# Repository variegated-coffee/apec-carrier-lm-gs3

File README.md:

# APEC Carrier Board for the La Marzocco GS3

*APEC carrier board R1A, rendered in KiCad.*

Espresso electronics are usually proprietary affairs with little to no expandability. The purpose of this project is to give everyone an open source alternative with lots of features and flexibility.

This board is a carrier for the [APEC SoM](https://github.com/variegated-coffee/apec-som), the All Purpose Espresso Controller System-on-Module. It replaces the control board of a La Marzocco GS3: it fits the machine's mains, sensor and actuator wiring, and the SoM does the rest. The SoM provides the RP2350B microcontroller, the ESP32-C6 radio, the ADS124S08 ADC, the FDC1004 capacitance-to-digital converter and a USB hub.

This project isn't affiliated with or endorsed by La Marzocco. "La Marzocco" and "GS3" are used only to say which machine the board is designed for.

## High-level features

* Mains side, on a 13-position terminal block (J2):
  * Three mechanical relays for the group, fill and tea solenoids (U9–U11, Panasonic ALDP112)
  * A 16 A relay for the stock rotary pump (K1)
  * On-board fuse (5×20 mm, clips F2/F3) and varistors on every switched output
  * On-board 12 V, 10 W AC/DC module (U5) for the low-voltage side
* Two SSR control outputs for the brew and service boilers (CN10, CN11)
* Isolated 24 V section, fed from an external 24 V supply (J5):
  * Two low-side switched 24 V outputs for (proportional) solenoids (CN13, CN14), driven through an ADuM3221 isolated gate driver - primarily intended for a proportional steam valve
  * A gear pump connector (CN9) with 5 V speed, direction and tacho signals, made for the FG304
* Sensors:
  * Two RTD inputs (PT1000, ratiometric, on the SoM's ADS124S08)
  * Two pressure transducer inputs (0.5–4.5 V, 5 V supply)
  * Two load cell inputs on an NAU7802 24-bit ADC, with their own ground
  * Two capacitive level inputs (tank and boiler) on the SoM's FDC1004
  * Flow meter, paddle switch and potentiometer inputs
* Display and expansion:
  * EyeSPI connectors for a display module (J13 2×10 header and J17 18-pin FFC) - preferably the [APEC LM GS3 HMI Module](https://github.com/variegated-coffee/apec-lm-gs3-hmi-module)
  * Two Qwiic connectors, a 4-pin I2C header, and a DS3231 RTC with a battery connector
  * microSD card slot
  * UART connector, pin compatible with the LM IoT module (J6)
* USB-C for programming and debugging. The board runs from USB alone for bench work.
* SWD header and a Femtoprobe footprint for the RP2350, and buttons for the RP2350's BOOTSEL and reset and the ESP32-C6's reset and boot mode
* Status LEDs for every output and power rail

[ENGINEERING-NOTES.md](ENGINEERING-NOTES.md) has the details, [IO.md](IO.md) the GPIO assignments, [MANUFACTURING-NOTES.md](MANUFACTURING-NOTES.md) how to build one, and [docs/INSTALLATION.md](docs/INSTALLATION.md) how to install it in a GS3.

## Project status

The current revision is R1A. It hasn't been manufactured yet; EV2 is the most recent revision that has been built. [CHANGELOG.md](CHANGELOG.md) lists what changed between revisions.

There are a few changes between EV2 and R1A, so at this time, rather than manufacturing this yourself, you should probably check in with the Variegated Coffee Discord server to see if someone is willing to share the risk.

The firmware is [developed separately](https://github.com/variegated-coffee/variegated-rs).

## ⚠️ Safety warning

This board switches mains voltage. It is intended to be installed inside an espresso machine, which also uses high-pressure hot water and steam. Mistakes in designing, building, wiring, or programming the board or the machine can cause electric shock, fire, burns, or scalding.

Mains voltage is present on the board whenever the machine is plugged in, including on the neutral side, which can carry line voltage with an unpolarised plug. Never work on the board or handle it while it's connected to mains. Never power it from mains outside a closed, earthed enclosure.

This board is not a safety component. Safety-critical protections, such as thermal cutouts, pressure relief and the machine's own fuses, must be kept and must work independently of this board and its firmware. Only build or use it if you are competent with mains electrical work and pressurised systems, and follow local electrical regulations.

## Notice

This repository contains design files only. It is not a finished product, and it has not been tested or certified for compliance with any regulation, including but not limited to CE, UKCA or FCC requirements.

Anyone who manufactures, assembles, or places a product based on these files on the market does so as the manufacturer of that product, and is solely responsible for its safety, conformity assessment, marking, documentation, and any legal obligations that follow. If you build or use it yourself, you do so at your own risk.

The APEC SoM includes a 2.4 GHz radio transceiver (ESP32-C6). Products using it are subject to radio equipment regulations in addition to other applicable requirements.

The designs are provided “as is” under the CERN-OHL-P v2. See sections 5.1 and 5.2 for the disclaimer of warranty and limitation of liability.

## Opening the design

The project is made with KiCad 10. Every library the design needs is either in this repository or a KiCad standard library, so it opens without extra setup. A few parts exist only as copies embedded in the schematic and PCB, because their library files can't be redistributed. KiCad reports their libraries as missing, which is expected. See [THIRD_PARTY.md](THIRD_PARTY.md).

Vendor 3D models aren't included either. [3d-models/README.md](3d-models/README.md) lists where to download them for complete 3D views.

## License

The design files and documentation in this repository are licensed under the CERN Open Hardware Licence Version 2 – Permissive (CERN-OHL-P-2.0); see [LICENSE.txt](LICENSE.txt).

Some library files come from third parties and keep their own licences; see [THIRD_PARTY.md](THIRD_PARTY.md).

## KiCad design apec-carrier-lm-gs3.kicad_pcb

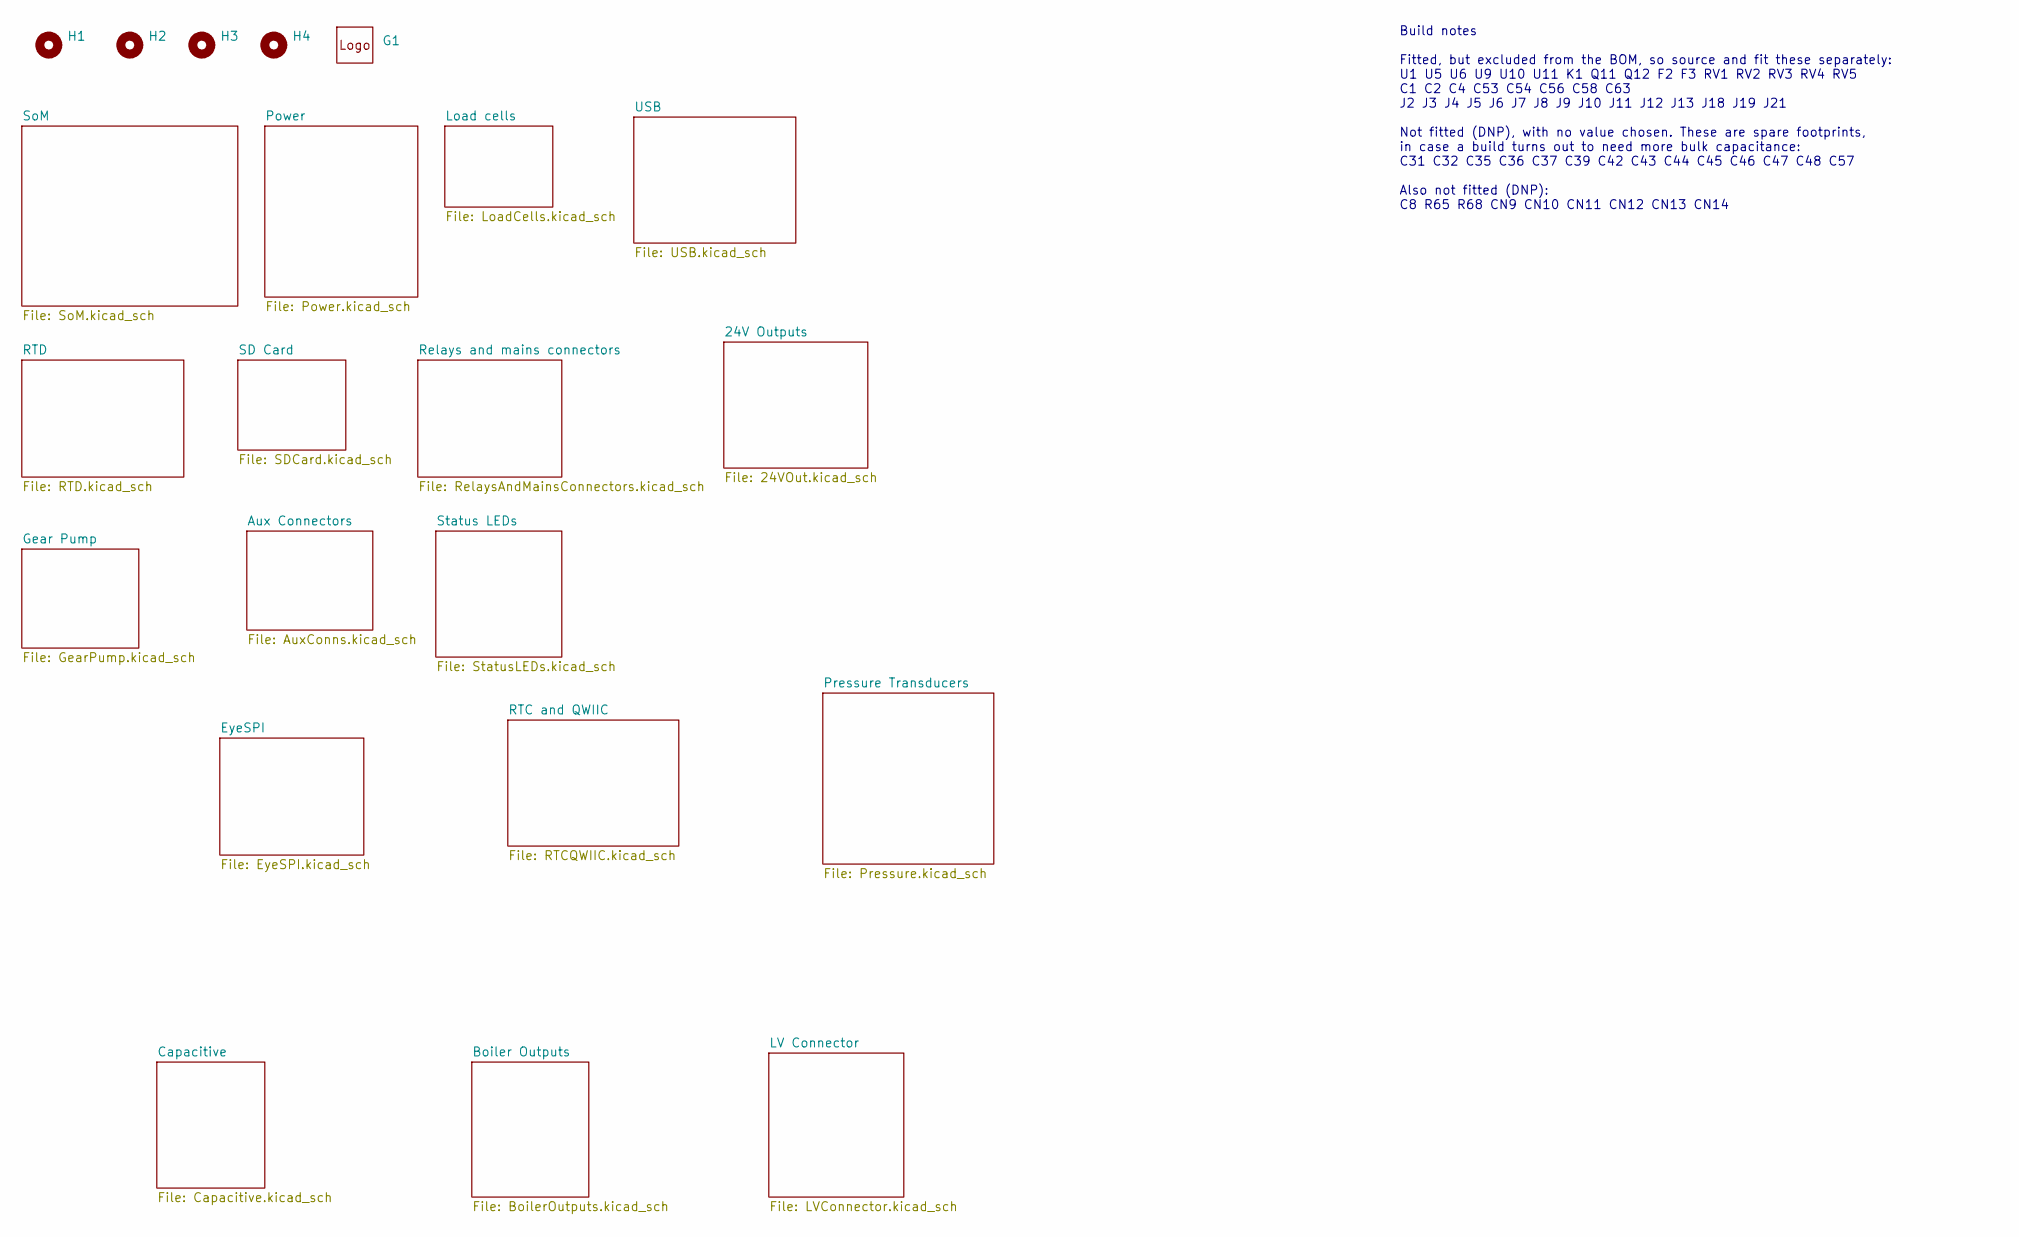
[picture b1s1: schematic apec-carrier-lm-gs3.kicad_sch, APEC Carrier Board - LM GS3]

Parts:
G1: VariegatedCoffeeLogo_Small
H1, H2, H3, H4: MountingHole_3.2mm_M3

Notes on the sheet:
Build notes Fitted, but excluded from the BOM, so source and fit these separately: U1 U5 U6 U9 U10 U11 K1 Q11 Q12 F2 F3 RV1 RV2 RV3 RV4 RV5 C1 C2 C4 C53 C54 C56 C58 C63 J2 J3 J4 J5 J6 J7 J8 J9 J10 J11 J12 J13 J18 J19 J21 Not fitted (DNP), with no value chosen. These are spare footprints, in case a 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

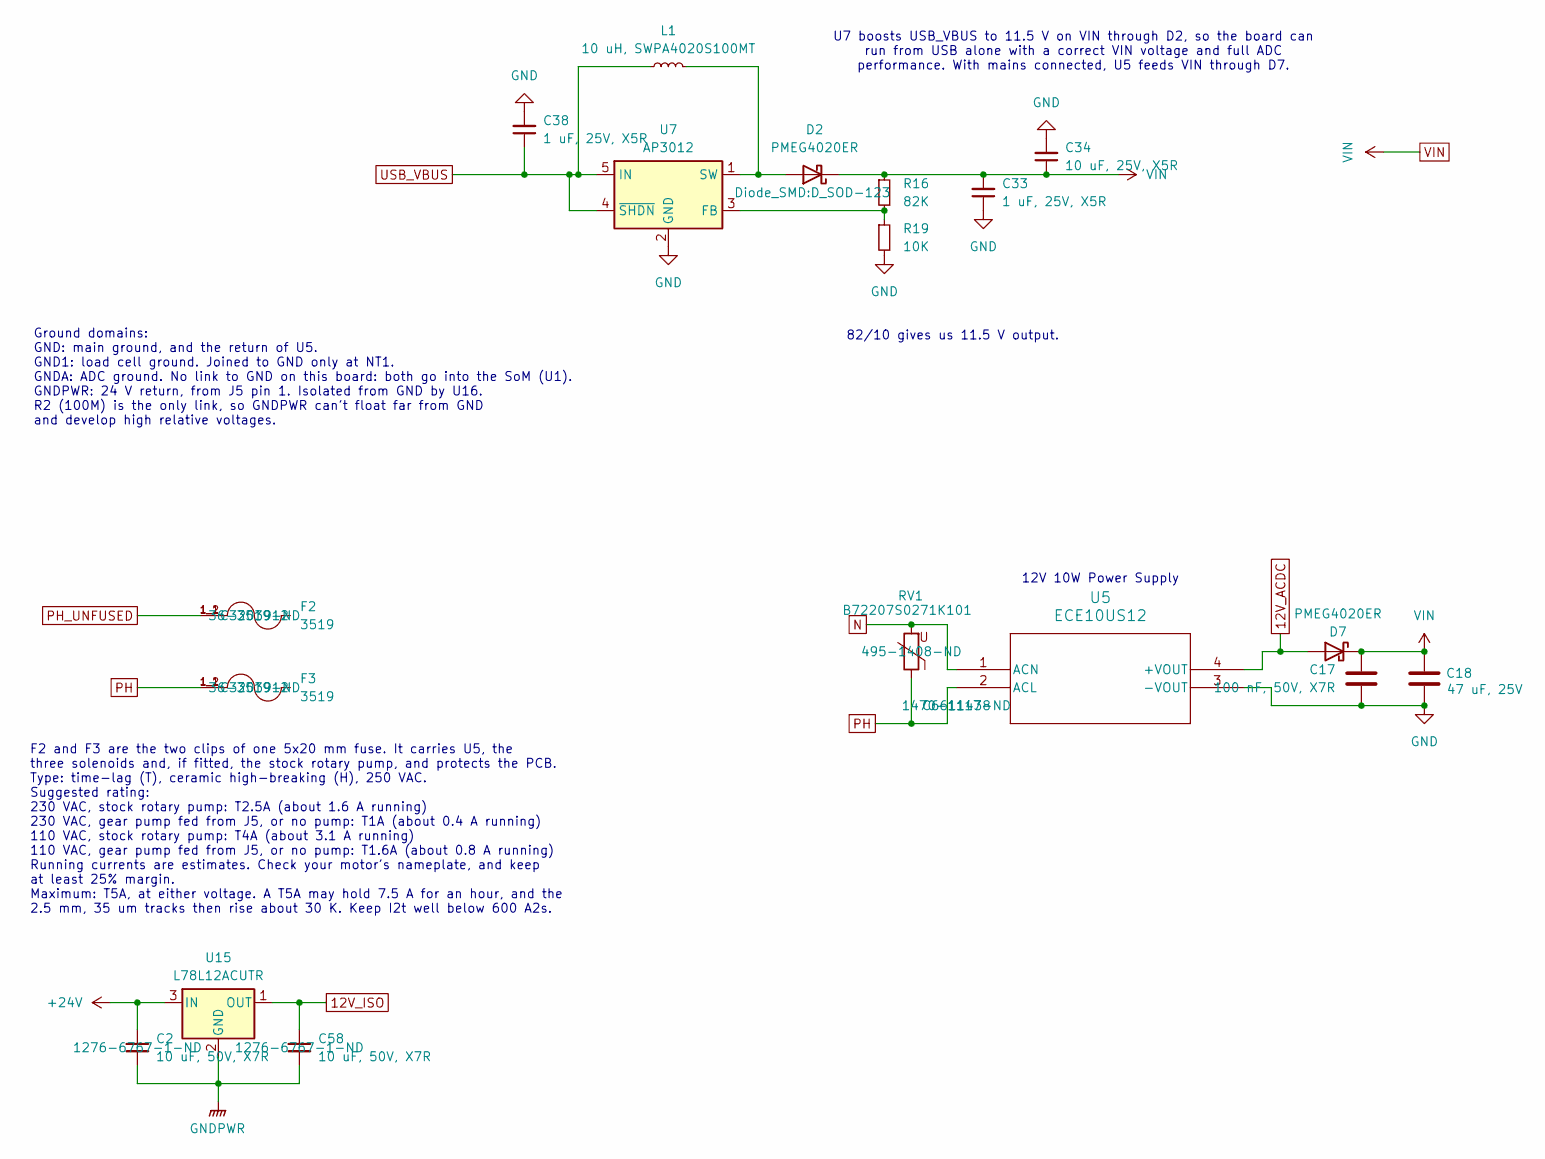
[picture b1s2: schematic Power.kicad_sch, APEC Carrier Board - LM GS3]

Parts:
C2, C58: 10 uF, 50V, X7R; C_1206_3216Metric; Digikey 1276-6767-1-ND
C17: 100 nF, 50V, X7R; C_0603_1608Metric; LCSC C14663
C18: 47 uF, 25V; C_1206_3216Metric; LCSC C76659
C33, C38: 1 uF, 25V, X5R; C_0603_1608Metric; LCSC C15849
C34: 10 uF, 25V, X5R; C_0805_2012Metric; LCSC C440198
D2, D7: PMEG4020ER; D_SOD-123; LCSC C255588
F2, F3: 3519; FUSE_3519; PARTREV D; LCSC C3203912
L1: 10 uH, SWPA4020S100MT; L_Sunlord_SWPA4020S; LCSC C82398
R16: 82K; R_0805_2012Metric; LCSC C17840
R19: 10K; R_0805_2012Metric; LCSC C17414
RV1: B72207S0271K101; RV_Disc_D9mm_W5.4mm_P5mm_Drill0.9mm; LCSC C125493
U5: ECE10US12; RELAY4_ECE10_XPR; LCSC C6611438
U7: AP3012; SOT-23-5; LCSC C460356
U15: L78L12ACUTR; SOT-89-3; LCSC C69601

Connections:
12V_ACDC: D7.2 (A), U5.4 (+VOUT); also elsewhere on the board
12V_ISO: C58.1, U15.1 (OUT); also elsewhere on the board
+24V: C2.1, U15.3 (IN); also elsewhere on the board
GND: C17.2, C18.2, C33.1, C34.2, C38.2, R19.2, U5.3 (-VOUT), U7.2 (GND); also elsewhere on the board
GNDPWR: C2.2, C58.2, U15.2 (GND); also elsewhere on the board
N: RV1.2, U5.1 (ACN); also elsewhere on the board
unnamed: D2.2 (A), L1.2, U7.1 (SW)
unnamed: R16.2, R19.1, U7.3 (FB)
PH: F3.1_1, F3.1_2, RV1.1, U5.2 (ACL); also elsewhere on the board
PH_UNFUSED: F2.1_1, F2.1_2; also elsewhere on the board
USB_VBUS: C38.1, L1.1, U7.4 (~SHDN), U7.5 (IN); also elsewhere on the board
VIN: C17.1, C18.1, C33.2, C34.1, D2.1 (K), D7.1 (K), R16.1; also elsewhere on the board

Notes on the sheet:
12V 10W Power Supply
U7 boosts USB_VBUS to 11.5 V on VIN through D2, so the board can run from USB alone with a correct VIN voltage and full ADC performance. With mains connected, U5 feeds VIN through D7.
F2 and F3 are the two clips of one 5x20 mm fuse. It carries U5, the three solenoids and, if fitted, the stock rotary pump, and protects the PCB. Type: time-lag (T), ceramic high-breaking (H), 250 VAC. Suggested rating: 230 VAC, stock rotary pump: T2.5A (about 1.6 A running) 230 VAC, gear pump fed f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
Ground domains: GND: main ground, and the return of U5. GND1: load cell ground. Joined to GND only at NT1. GNDA: ADC ground. No link to GND on this board: both go into the SoM (U1). GNDPWR: 24 V return, from J5 pin 1. Isolated from GND by U16. R2 (100M) is the only link, so GNDPWR can't float far f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
82/10 gives us 11.5 V output.

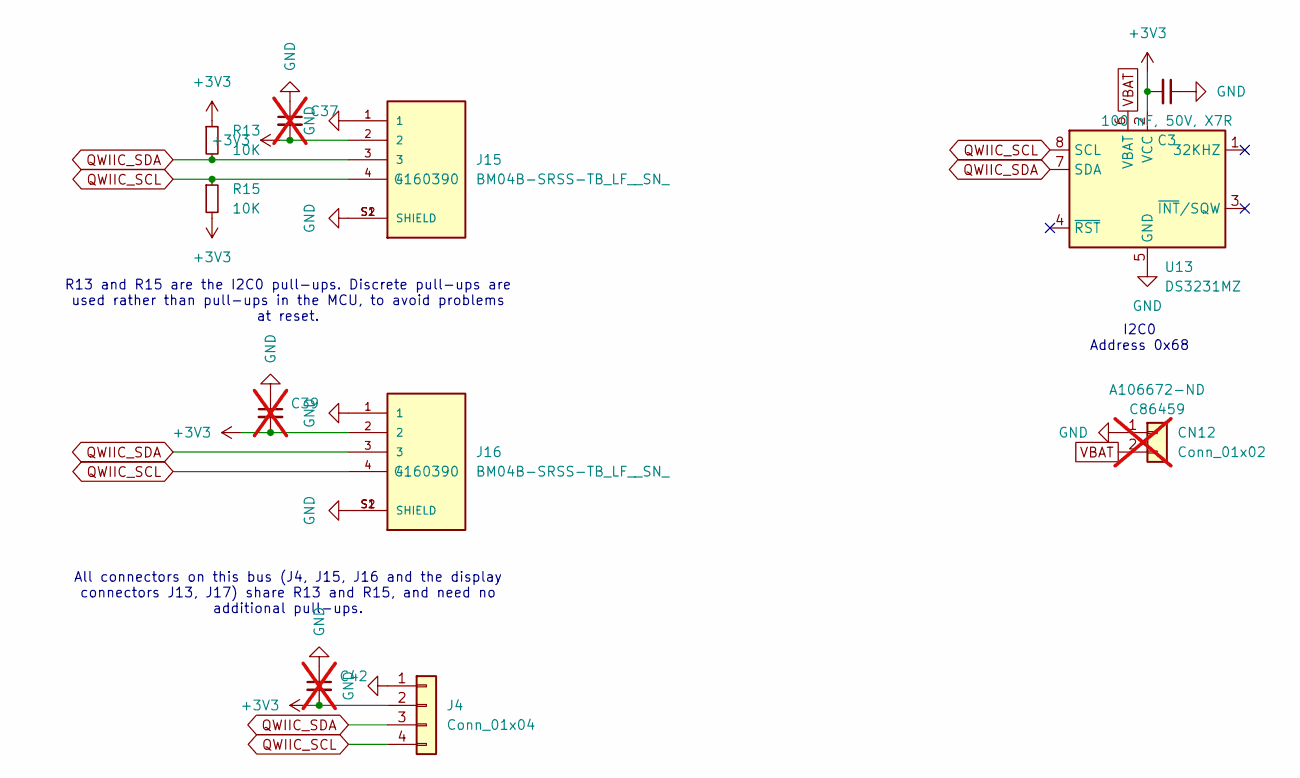
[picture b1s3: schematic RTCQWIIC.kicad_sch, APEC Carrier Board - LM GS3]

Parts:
C3: 100 nF, 50V, X7R; C_0603_1608Metric; LCSC C14663
C37, C39, C42: C_1206_3216Metric_Pad1.33x1.80mm_HandSolder; not fitted
CN12: Conn_01x02; TE_280370-1; LCSC C86459; not fitted
J4: Conn_01x04; PinHeader_1x04_P2.54mm_Vertical
J15, J16: BM04B-SRSS-TB_LF__SN_; JST_BM04B-SRSS-TB(LF)(SN); PARTREV N/A; LCSC C160390
R13, R15: 10K; R_0402_1005Metric; LCSC C25744
U13: DS3231MZ; SOIC-8_3.9x4.9mm_P1.27mm; LCSC C107410

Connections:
+3V3: C3.2, C37.2, C39.2, C42.2, J4.2, J15.2, J16.2, R13.1, R15.2, U13.2 (VCC); also elsewhere on the board
GND: C3.1, C37.1, C39.1, C42.1, CN12.1, J4.1, J15.1, J15.S1 (SHIELD), J15.S2 (SHIELD), J16.1, J16.S1 (SHIELD), J16.S2 (SHIELD), U13.5 (GND); also elsewhere on the board
QWIIC_SCL: J4.4, J15.4, J16.4, R15.1, U13.8 (SCL); also elsewhere on the board
QWIIC_SDA: J4.3, J15.3, J16.3, R13.2, U13.7 (SDA); also elsewhere on the board
VBAT: CN12.2, U13.6 (VBAT)

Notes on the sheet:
I2C0 Address 0x68
All connectors on this bus (J4, J15, J16 and the display connectors J13, J17) share R13 and R15, and need no additional pull-ups.
R13 and R15 are the I2C0 pull-ups. Discrete pull-ups are used rather than pull-ups in the MCU, to avoid problems at reset.

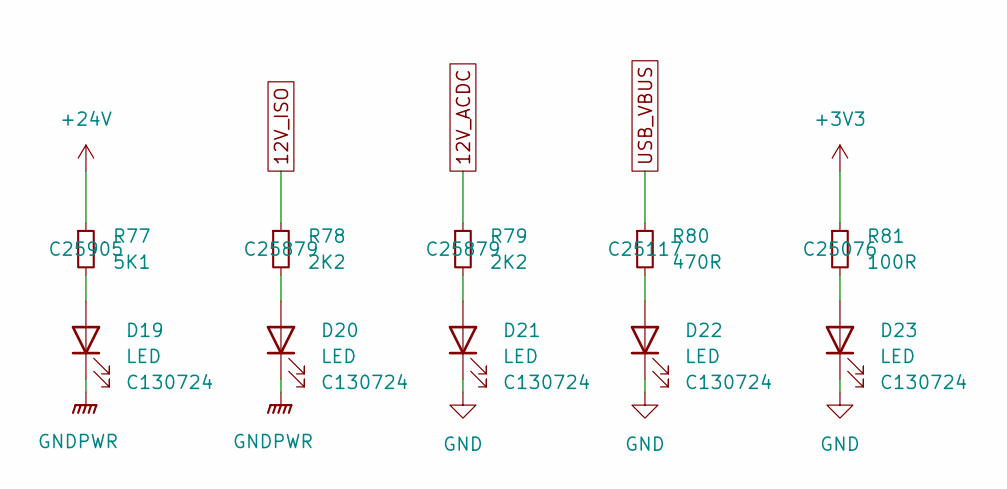
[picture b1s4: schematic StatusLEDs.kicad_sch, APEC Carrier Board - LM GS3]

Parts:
D19, D20, D21, D22, D23: LED; LED_0402_1005Metric; LCSC C130724
R77: 5K1; R_0402_1005Metric; LCSC C25905
R78, R79: 2K2; R_0402_1005Metric; LCSC C25879
R80: 470R; R_0402_1005Metric; LCSC C25117
R81: 100R; R_0402_1005Metric; LCSC C25076

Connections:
12V_ACDC: R79.1; also elsewhere on the board
12V_ISO: R78.1; also elsewhere on the board
+3V3: R81.1; also elsewhere on the board
+24V: R77.1; also elsewhere on the board
GND: D21.1 (K), D22.1 (K), D23.1 (K); also elsewhere on the board
GNDPWR: D19.1 (K), D20.1 (K); also elsewhere on the board
unnamed: D19.2 (A), R77.2
unnamed: D20.2 (A), R78.2
unnamed: D21.2 (A), R79.2
unnamed: D22.2 (A), R80.2
unnamed: D23.2 (A), R81.2
USB_VBUS: R80.1; also elsewhere on the board

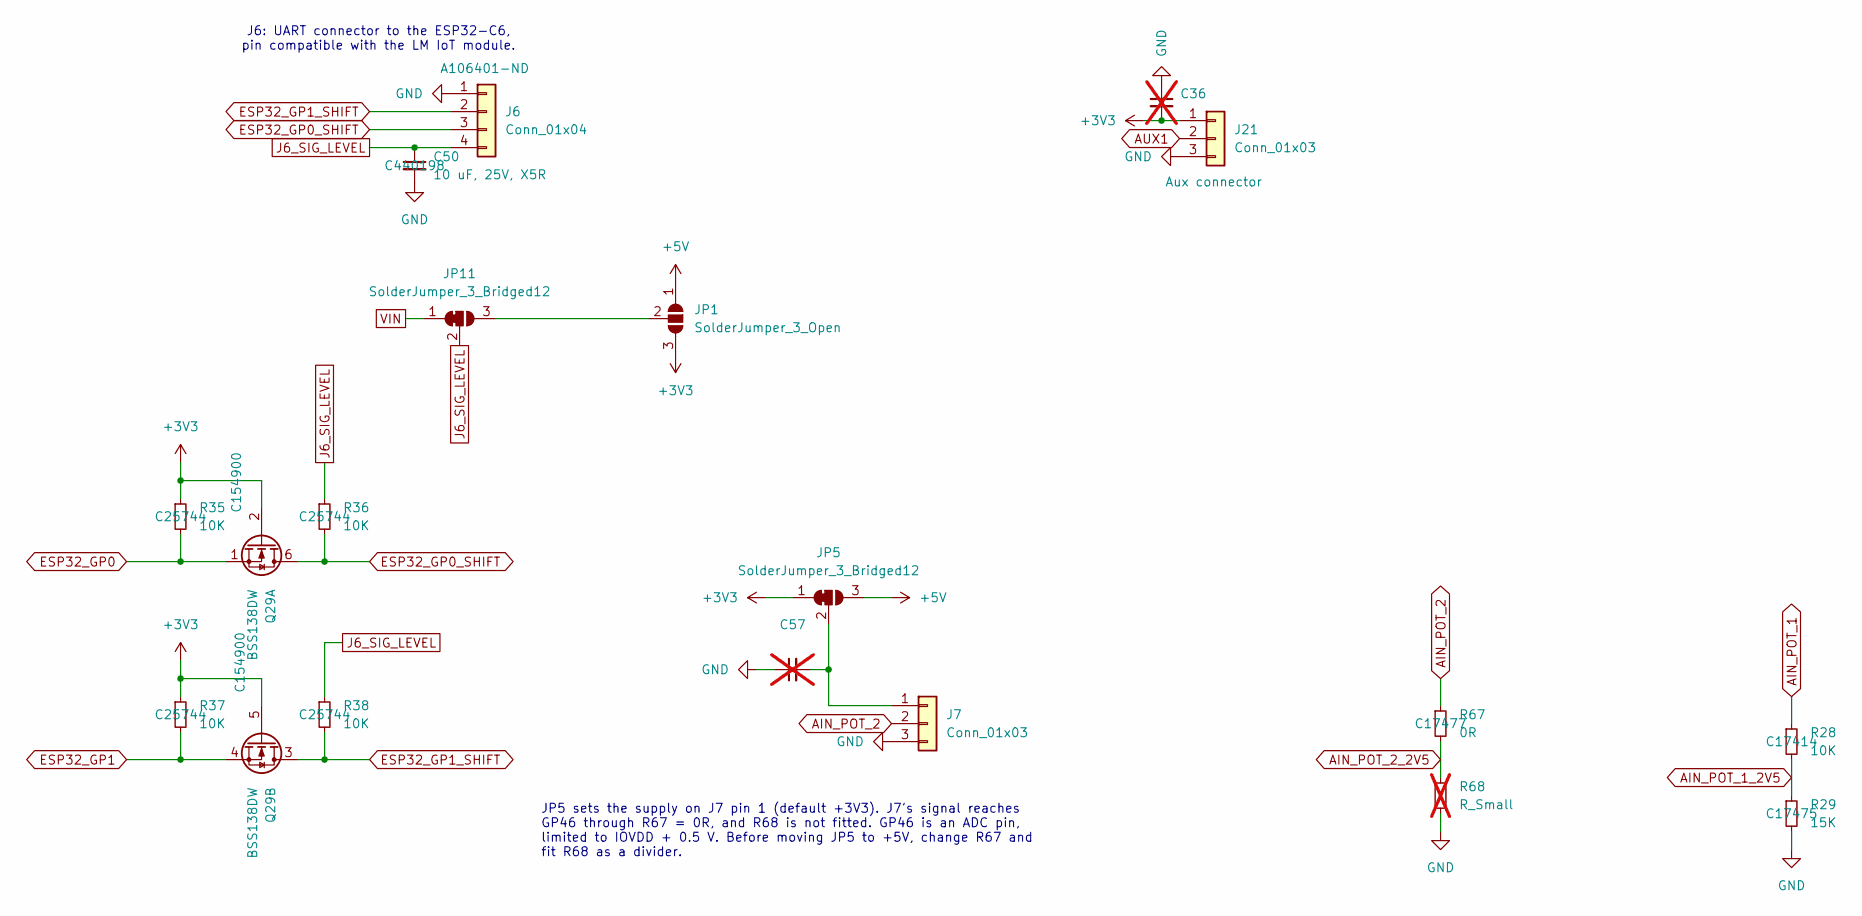
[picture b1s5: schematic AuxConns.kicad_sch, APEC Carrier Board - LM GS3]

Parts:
C36, C57: C_1206_3216Metric_Pad1.33x1.80mm_HandSolder; not fitted
C50: 10 uF, 25V, X5R; C_0805_2012Metric; LCSC C440198
J6: Conn_01x04; TE_280371-2; Digikey A106401-ND
J7, J21: Conn_01x03; PinHeader_1x03_P2.54mm_Vertical
JP1: SolderJumper_3_Open; SolderJumper-3_P1.3mm_Open_Pad1.0x1.5mm_NumberLabels
JP5: SolderJumper_3_Bridged12; SolderJumper-3_P1.3mm_Bridged2Bar12_Pad1.0x1.5mm
JP11: SolderJumper_3_Bridged12; SolderJumper-3_P1.3mm_Bridged2Bar12_Pad1.0x1.5mm_NumberLabe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
Q29: BSS138DW; SOT-363_SC-70-6; LCSC C154900
R28: 10K; R_0805_2012Metric; LCSC C17414
R29: 15K; R_0805_2012Metric; LCSC C17475
R35, R36, R37, R38: 10K; R_0402_1005Metric; LCSC C25744
R67: 0R; R_0805_2012Metric; LCSC C17477
R68: R_Small; R_0805_2012Metric; not fitted

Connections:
+3V3: C36.2, J21.1, JP1.3 (B), JP5.1 (A), Q29.2 (G), Q29.5 (G), R35.1, R37.1; also elsewhere on the board
+5V: JP1.1 (A), JP5.3 (B); also elsewhere on the board
AIN_POT_1: R28.1; also elsewhere on the board
AIN_POT_1_2V5: R28.2, R29.1; also elsewhere on the board
AIN_POT_2: J7.2, R67.1
AIN_POT_2_2V5: R67.2, R68.1; also elsewhere on the board
AUX1: J21.2; also elsewhere on the board
ESP32_GP0: Q29.1 (S), R35.2; also elsewhere on the board
ESP32_GP0_SHIFT: J6.3, Q29.6 (D), R36.2
ESP32_GP1: Q29.4 (S), R37.2; also elsewhere on the board
ESP32_GP1_SHIFT: J6.2, Q29.3 (D), R38.2
GND: C36.1, C50.2, C57.1, J6.1, J7.3, J21.3, R29.2, R68.2; also elsewhere on the board
J6_SIG_LEVEL: C50.1, J6.4, JP11.2 (C), R36.1, R38.1
unnamed: C57.2, J7.1, JP5.2 (C)
unnamed: JP1.2 (C), JP11.3 (B)
VIN: JP11.1 (A); also elsewhere on the board

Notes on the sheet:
JP5 sets the supply on J7 pin 1 (default +3V3). J7's signal reaches GP46 through R67 = 0R, and R68 is not fitted. GP46 is an ADC pin, limited to IOVDD + 0.5 V. Before moving JP5 to +5V, change R67 and fit R68 as a divider.
J6: UART connector to the ESP32-C6, pin compatible with the LM IoT module.

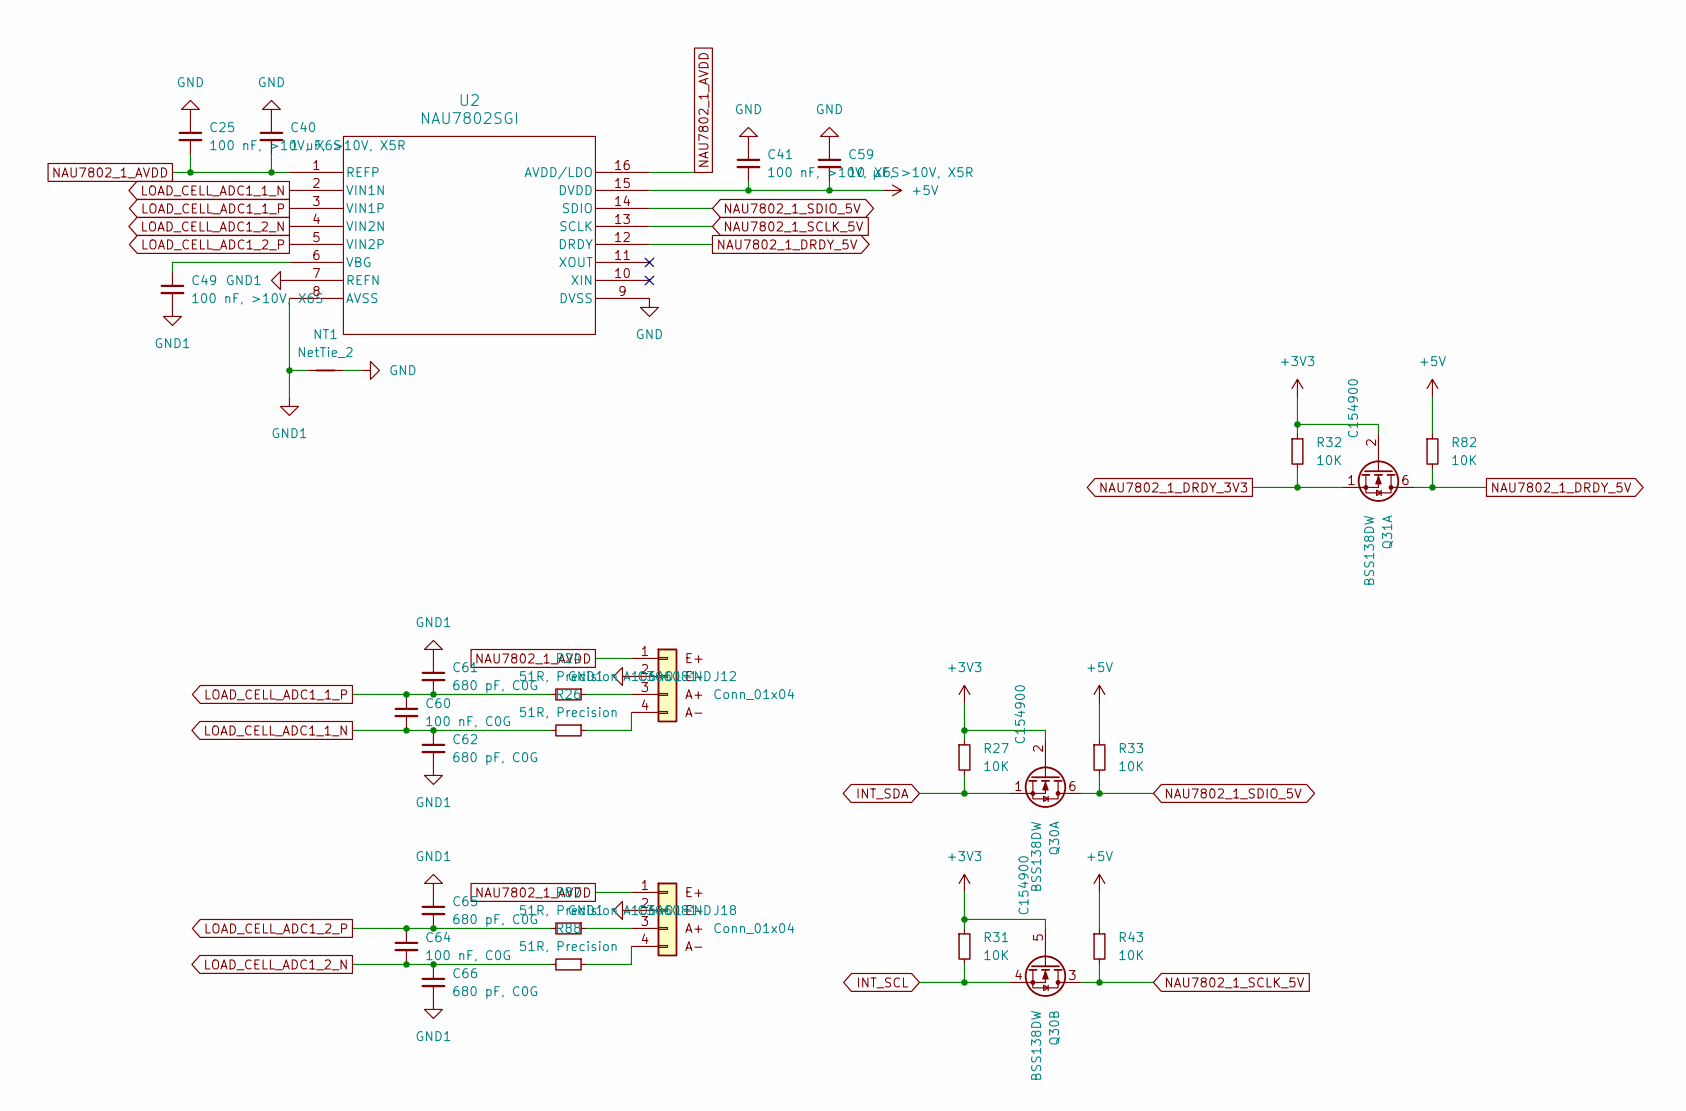
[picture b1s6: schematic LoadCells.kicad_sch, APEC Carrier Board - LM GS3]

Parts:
C25, C41, C49: 100 nF, >10V, X6S; C_0402_1005Metric; LCSC C1525
C40: 1 uF, >10V, X5R; C_0402_1005Metric; LCSC C52923
C59: 10 µF, >10V, X5R; C_0805_2012Metric; LCSC C440198
C60, C64: 100 nF, C0G; C_1206_3216Metric; LCSC C97946
C61, C62, C65, C66: 680 pF, C0G; C_1206_3216Metric; LCSC C326939
J12, J18: Conn_01x04; TE_280371-2; Digikey A106401-ND
NT1: NetTie_2; NetTie-2_SMD_Pad0.5mm
Q30, Q31: BSS138DW; SOT-363_SC-70-6; LCSC C154900
R24, R26, R87, R88: 51R, Precision; R_1206_3216Metric; LCSC C2828901
R27, R31, R32, R33, R43, R82: 10K; R_0402_1005Metric; LCSC C25744
U2: NAU7802SGI; SOP-16_4.4x10.4mm_P1.27mm; LCSC C5180029

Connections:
+3V3: Q30.2 (G), Q30.5 (G), Q31.2 (G), R27.1, R31.1, R32.1; also elsewhere on the board
+5V: C41.2, C59.2, R33.1, R43.1, R82.1, U2.15 (DVDD); also elsewhere on the board
GND: C25.1, C40.1, C41.1, C59.1, NT1.2, U2.9 (DVSS); also elsewhere on the board
GND1: C49.2, C61.1, C62.2, C65.1, C66.2, J12.2, J18.2, NT1.1, U2.7 (REFN), U2.8 (AVSS)
INT_SCL: Q30.4 (S), R31.2; also elsewhere on the board
INT_SDA: Q30.1 (S), R27.2; also elsewhere on the board
LOAD_CELL_ADC1_1_N: C60.2, C62.1, R26.2, U2.2 (VIN1N)
LOAD_CELL_ADC1_1_P: C60.1, C61.2, R24.2, U2.3 (VIN1P)
LOAD_CELL_ADC1_2_N: C64.2, C66.1, R88.2, U2.4 (VIN2N)
LOAD_CELL_ADC1_2_P: C64.1, C65.2, R87.2, U2.5 (VIN2P)
NAU7802_1_AVDD: C25.2, C40.2, J12.1, J18.1, U2.1 (REFP), U2.16 (AVDD/LDO)
NAU7802_1_DRDY_3V3: Q31.1 (S), R32.2; also elsewhere on the board
NAU7802_1_DRDY_5V: Q31.6 (D), R82.2, U2.12 (DRDY)
NAU7802_1_SCLK_5V: Q30.3 (D), R43.2, U2.13 (SCLK)
NAU7802_1_SDIO_5V: Q30.6 (D), R33.2, U2.14 (SDIO)
unnamed: J12.3, R24.1
unnamed: J12.4, R26.1
unnamed: J18.3, R87.1
unnamed: J18.4, R88.1
unnamed: C49.1, U2.6 (VBG)

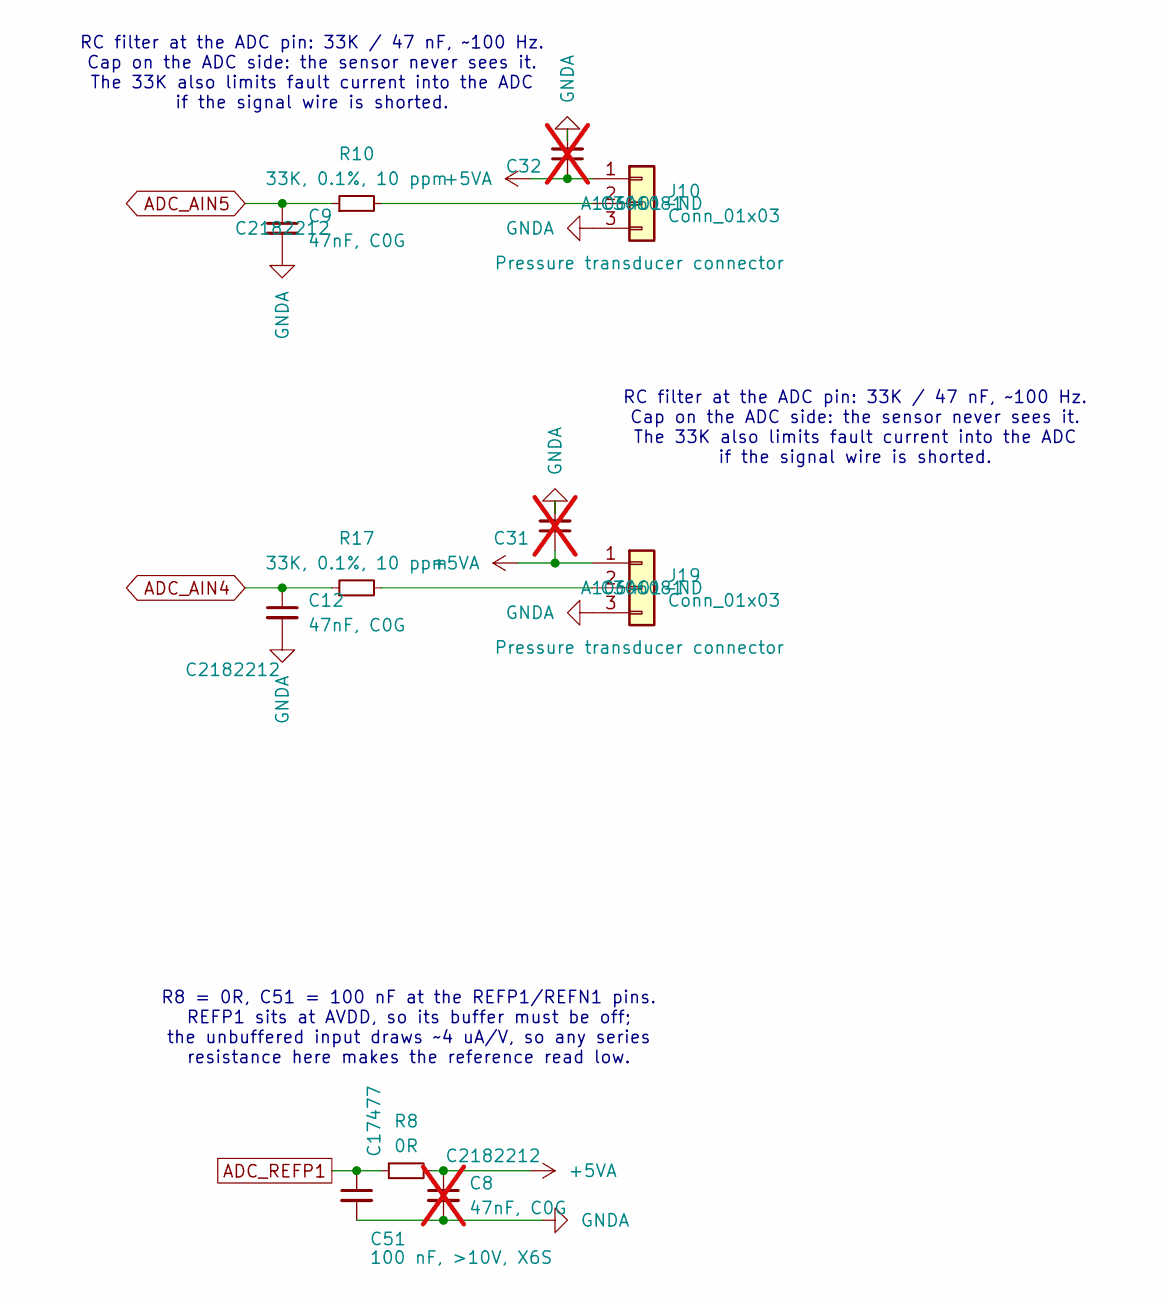
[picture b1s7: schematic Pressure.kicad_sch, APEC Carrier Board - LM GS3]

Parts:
C8: 47nF, C0G; C_0805_2012Metric_Pad1.18x1.45mm_HandSolder; LCSC C2182212; not fitted
C9, C12: 47nF, C0G; C_0805_2012Metric_Pad1.18x1.45mm_HandSolder; LCSC C2182212
C31, C32: C_1206_3216Metric_Pad1.33x1.80mm_HandSolder; not fitted
C51: 100 nF, >10V, X6S; C_0402_1005Metric; LCSC C1525
J10, J19: Conn_01x03; TE_280371-2; LCSC C306081
R8: 0R; R_0805_2012Metric_Pad1.20x1.40mm_HandSolder; LCSC C17477
R10, R17: 33K, 0.1%, 10 ppm; R_0805_2012Metric_Pad1.20x1.40mm_HandSolder; LCSC C351577

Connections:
+5VA: C8.1, C31.1, C32.1, J10.1, J19.1, R8.2; also elsewhere on the board
ADC_AIN4: C12.1, R17.1; also elsewhere on the board
ADC_AIN5: C9.1, R10.1; also elsewhere on the board
ADC_REFP1: C51.1, R8.1; also elsewhere on the board
GNDA: C8.2, C9.2, C12.2, C31.2, C32.2, C51.2, J10.3, J19.3; also elsewhere on the board
unnamed: J10.2, R10.2
unnamed: J19.2, R17.2

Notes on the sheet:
RC filter at the ADC pin: 33K / 47 nF, ~100 Hz. Cap on the ADC side: the sensor never sees it. The 33K also limits fault current into the ADC if the signal wire is shorted.
R8 = 0R, C51 = 100 nF at the REFP1/REFN1 pins. REFP1 sits at AVDD, so its buffer must be off; the unbuffered input draws ~4 uA/V, so any series resistance here makes the reference read low.

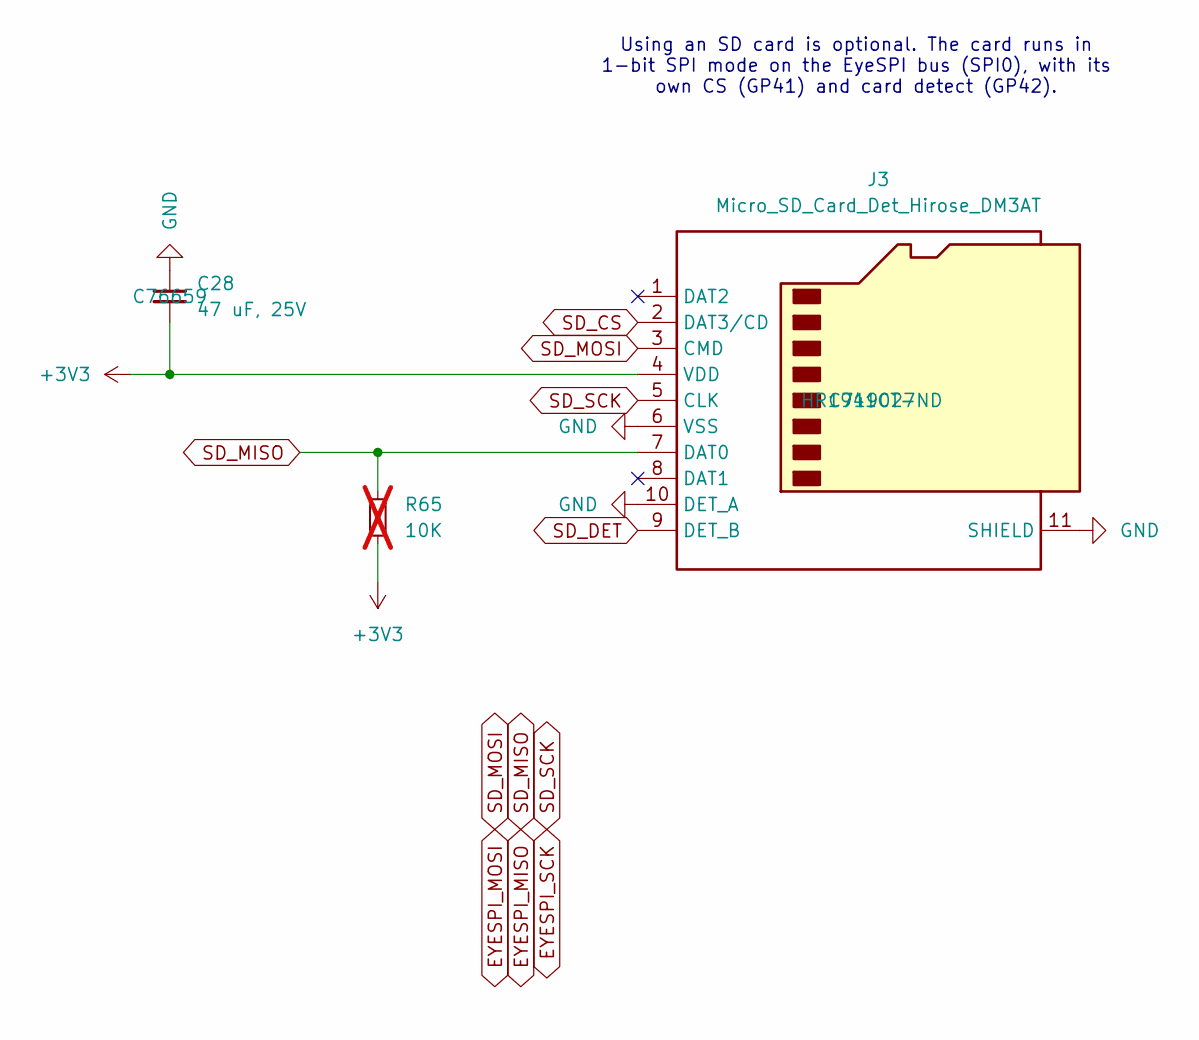
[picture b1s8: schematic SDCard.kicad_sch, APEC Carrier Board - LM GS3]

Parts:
C28: 47 uF, 25V; C_1206_3216Metric; LCSC C76659
J3: Micro_SD_Card_Det_Hirose_DM3AT; microSD_HC_Hirose_DM3D-SF; LCSC C719027
R65: 10K; R_0805_2012Metric_Pad1.20x1.40mm_HandSolder; not fitted

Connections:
+3V3: C28.2, J3.4 (VDD), R65.2; also elsewhere on the board
EYESPI_MISO: J3.7 (DAT0), R65.1; also elsewhere on the board
EYESPI_MOSI: J3.3 (CMD); also elsewhere on the board
EYESPI_SCK: J3.5 (CLK); also elsewhere on the board
GND: C28.1, J3.6 (VSS), J3.10 (DET_A), J3.11 (SHIELD); also elsewhere on the board
SD_CS: J3.2 (DAT3/CD); also elsewhere on the board
SD_DET: J3.9 (DET_B); also elsewhere on the board

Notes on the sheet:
Using an SD card is optional. The card runs in 1-bit SPI mode on the EyeSPI bus (SPI0), with its own CS (GP41) and card detect (GP42).

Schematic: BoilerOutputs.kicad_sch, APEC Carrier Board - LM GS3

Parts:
C43, C44: C_1206_3216Metric_Pad1.33x1.80mm_HandSolder; not fitted
CN10, CN11: Conn_01x02; TE_280370-1; LCSC C86459; not fitted
D15, D16: LED; LED_0402_1005Metric; LCSC C130724
Q26, Q27: BSS138DW; SOT-363_SC-70-6; LCSC C154900
R49, R50: 10K; R_0402_1005Metric; LCSC C25744
R62, R63: 100R; R_0402_1005Metric; LCSC C25076

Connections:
+3V3: R62.1, R63.1; also elsewhere on the board
BREW_BOILER_EN: Q27.2 (G), Q27.5 (G), R50.1; also elsewhere on the board
GND: C43.1, C44.1, Q26.1 (S), Q26.4 (S), Q27.1 (S), Q27.4 (S), R49.2, R50.2; also elsewhere on the board
unnamed: CN10.1, Q27.6 (D)
unnamed: CN11.2, Q26.6 (D)
unnamed: D15.2 (A), R62.2
unnamed: D15.1 (K), Q27.3 (D)
unnamed: D16.2 (A), R63.2
unnamed: D16.1 (K), Q26.3 (D)
SERVICE_BOILER_EN: Q26.2 (G), Q26.5 (G), R49.1; also elsewhere on the board
VIN: C43.2, C44.2, CN10.2, CN11.1; also elsewhere on the board

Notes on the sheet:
Note that the Service boiler SSR connector has reverse polarity compared to the brew boiler SSR connector!
RP2350 erratum E9 and pull-downs R49, R50: The 10K pull-downs hold these outputs low despite E9. E9 (A2 stepping only) needs a pin's input buffer on, its output off and its voltage between the logic levels. After power-up or reset the input buffer is off, so the pull-down holds the pin low, and onc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

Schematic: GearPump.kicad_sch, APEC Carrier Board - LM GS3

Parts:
C11: 10nF, 50V, X7R; C_0603_1608Metric; LCSC C57112
C56: 10 uF, 50V, X7R; C_1206_3216Metric_Pad1.33x1.80mm_HandSolder; Digikey 1276-6767-1-ND
CN9: Conn_02x04_Odd_Even; SAMTEC_IPL1-104-01-L-D-K; LCSC C17671197; not fitted
J5: Phoenix 1758018; TerminalBlock_Phoenix_MKDS-1,5-2_1x02_P5.00mm_Horizontal; Digikey 277-1073-ND
R2: 100M, 75V; R_0603_1608Metric_Pad0.98x0.95mm_HandSolder; LCSC C422892
R11, R12: 10K; R_0402_1005Metric; LCSC C25744
R14: 51K; R_0402_1005Metric; LCSC C25794
U3, U4: 74LV1T125; SOT-23-5_HandSoldering; LCSC C473338

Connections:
+5V: U3.5 (VCC), U4.5 (VCC); also elsewhere on the board
+24V: C56.1, CN9.1, J5.2; also elsewhere on the board
FG_DIRECTION_3V3: R12.2, U4.2; also elsewhere on the board
FG_DIRECTION_5V: CN9.4, U4.4
FG_SPEED_IN_3V3: R11.2, U3.2; also elsewhere on the board
FG_SPEED_IN_5V: C11.1, CN9.7, R14.2
FG_TACHO_OUT_5V: CN9.8; also elsewhere on the board
GND: C11.2, CN9.3, R2.2, R11.1, R12.1, U3.1, U3.3 (GND), U4.1, U4.3 (GND); also elsewhere on the board
GNDPWR: C56.2, CN9.5, J5.1, R2.1; also elsewhere on the board
unnamed: R14.1, U3.4

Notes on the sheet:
FG_TACHO_OUT_5V goes straight to GP25 (U1 pin 71), with no level shifter or pull-up on this board. GP25 is a fault-tolerant pin: it accepts up to 5.5 V only while IOVDD is at 3.3 V (RP2350 datasheet).
FG304: keep the FG signal ground (pin 3, GND) and the motor return (pin 5, GNDPWR) separate. Required by the FG304 datasheet.
U3 and U4 are 74LV1T125 parts drawn with the 74LVC1G125 symbol. The pinouts are the same (SN74LV1T125 datasheet).
J5 brings +24V (pin 2) and GNDPWR (pin 1) in from outside the board. Nothing on this board generates +24V. It feeds CN9, CN13, CN14 and U15 (net class 24V-2A).
RP2350 erratum E9 and pull-downs R11, R12: The 10K pull-downs hold these outputs low despite E9. E9 (A2 stepping only) needs a pin's input buffer on, its output off and its voltage between the logic levels. After power-up or reset the input buffer is off, so the pull-down holds the pin low, and onc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

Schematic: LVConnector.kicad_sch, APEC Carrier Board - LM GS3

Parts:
C35: C_1206_3216Metric_Pad1.33x1.80mm_HandSolder; not fitted
J9: Phoenix 1753550; TerminalBlock_Phoenix_MKDS-1,5-8_1x08_P5.00mm_Horizontal; Digikey 277-1079-ND
JP2: SolderJumper_3_Bridged12; SolderJumper-3_P1.3mm_Bridged2Bar12_Pad1.0x1.5mm
R57: 10K; R_0805_2012Metric; LCSC C17414

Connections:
+3V3: JP2.3 (B); also elsewhere on the board
+5V: JP2.1 (A); also elsewhere on the board
AIN_POT_1: J9.2; also elsewhere on the board
BOILER_CIN: J9.5; also elsewhere on the board
FLOW_METER_DATA: J9.3, R57.2; also elsewhere on the board
FLOW_METER_VCC: C35.2, J9.6, JP2.2 (C), R57.1
GND: C35.1, J9.7; also elsewhere on the board
MP_PADDLE_SW: J9.1; also elsewhere on the board
TANK_CIN: J9.4; also elsewhere on the board
TANK_REF: J9.8; also elsewhere on the board

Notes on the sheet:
RP2350 erratum E9 and the paddle switch (MP_PADDLE_SW, J9 pin 1, GP20): This board has no pull resistor on MP_PADDLE_SW, and it isn't known whether the GS3 MP's paddle switch needs a pull-up or a pull-down. The RP2350's internal pull-up works on every stepping, but on the A2 stepping E9 stops the i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

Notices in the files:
24VOut.kicad_sch:
License: OHL-P
